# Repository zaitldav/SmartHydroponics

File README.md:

# SmartHydroponics
A controller for small autonomous hydroponics.

## Mindmap

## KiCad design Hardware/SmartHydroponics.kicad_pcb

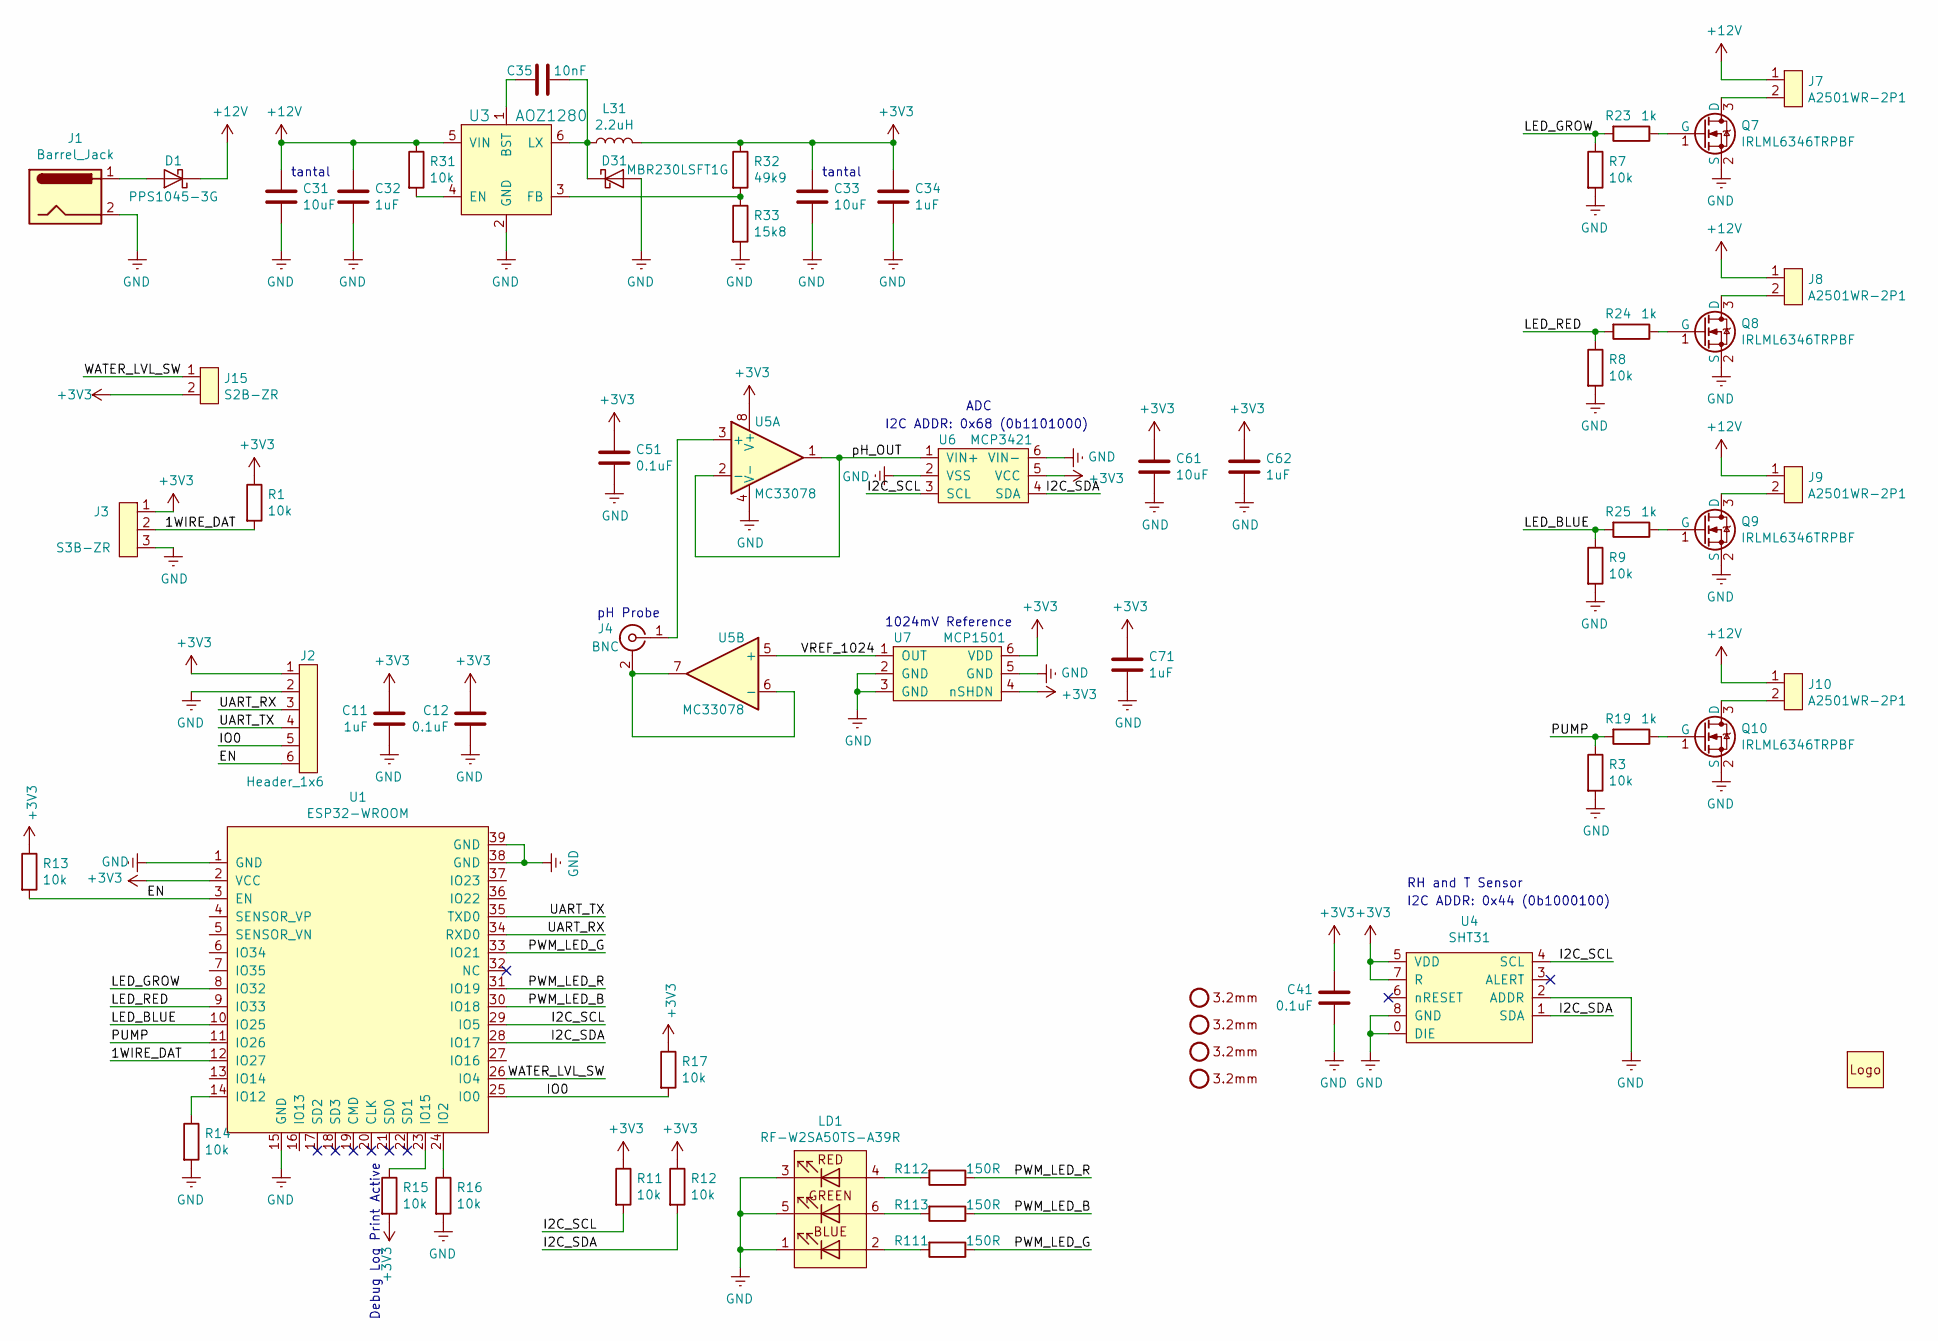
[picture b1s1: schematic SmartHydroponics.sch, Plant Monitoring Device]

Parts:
C11, C32, C34, C62, C71: 1uF; C0603
C12, C41, C51: 0.1uF; C0603
C31, C33, C61: 10uF; C1210
C35: 10nF; C0603
D1: PPS1045-3G; TO-277-3
D31: MBR230LSFT1G; SOD-123
H1, H2, H3, H4: Mounting_hole_unplated_3,2mm
H111: Mr_Gardener_Logo_Small; mr_hydrogardener_logo_12mm
J1: Barrel_Jack; BarrelJack_Horizontal
J2: Header_1x6; Header_1x06_P2.54mm
J3: S3B-ZR
J4: BNC; TE_BNC
J7, J8, J9, J10: A2501WR-2P1
J15: S2B-ZR
L31: 2.2uH; L1210
LD1: RF-W2SA50TS-A39R
Q7, Q8, Q9, Q10: IRLML6346TRPBF; SOT-23
R1, R3, R7, R8, R9, R11, R12, R13, R14, R15, R16, R17, R31: 10k; R0603
R19, R23, R24, R25: 1k; R0603
R32: 49k9; R0603
R33: 15k8; R0603
R111, R112, R113: 150R; R0603
U1: ESP32-WROOM
U3: AOZ1280; SOT-23-6
U4: SHT31
U5: MC33078; SOIC-8
U6: MCP3421; SOT-23-6
U7: MCP1501; SOT-23-6

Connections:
+3V3: C11.1, C12.1, C33.1, C34.1, C41.1, C51.1, C61.1, C62.1, C71.1, J2.1, J3.1, J15.2, L31.2, R1.1, R11.1, R12.1, R13.1, R15.2, R17.1, R32.1, U1.2 (VCC), U4.5 (VDD), U4.7 (R), U5.8 (V+), U6.5 (VCC), U7.4 (nSHDN), U7.6 (VDD)
+12V: C31.1, C32.1, D1.1 (K), J7.1, J8.1, J9.1, J10.1, R31.1, U3.5 (VIN)
/1WIRE_DAT: J3.2, R1.2, U1.12 (IO27)
/EN: J2.6, R13.2, U1.3 (EN)
/I2C_SCL: R11.2, U1.29 (IO5), U4.4 (SCL), U6.3 (SCL)
/I2C_SDA: R12.2, U1.28 (IO17), U4.1 (SDA), U6.4 (SDA)
/IO0: J2.5, R17.2, U1.25 (IO0)
/LED_BLUE: R9.1, R25.2, U1.10 (IO25)
/LED_GROW: R7.1, R23.2, U1.8 (IO32)
/LED_RED: R8.1, R24.2, U1.9 (IO33)
/PUMP: R3.1, R19.2, U1.11 (IO26)
/PWM_LED_B: R113.1, U1.30 (IO18)
/PWM_LED_G: R111.1, U1.33 (IO21)
/PWM_LED_R: R112.1, U1.31 (IO19)
/UART_RX: J2.3, U1.34 (RXD0)
/UART_TX: J2.4, U1.35 (TXD0)
/VREF_1024: U5.5 (+), U7.1 (OUT)
/WATER_LVL_SW: J15.1, U1.26 (IO4)
/pH_OUT: U5.1, U5.2 (-), U6.1 (VIN+)
GND: C11.2, C12.2, C31.2, C32.2, C33.2, C34.2, C41.2, C51.2, C61.2, C62.2, C71.2, D31.2 (A), J1.2, J2.2, J3.3, LD1.1 (K), LD1.3 (K), LD1.5 (K), Q7.2 (S), Q8.2 (S), Q9.2 (S), Q10.2 (S), R3.2, R7.2, R8.2, R9.2, R14.2, R16.2, R33.2, U1.1 (GND), U1.15 (GND), U1.38 (GND), U1.39 (GND), U3.2 (GND), U4.0 (DIE), U4.2 (ADDR), U4.8 (GND), U5.4 (V-), U6.2 (VSS), U6.6 (VIN-), U7.2 (GND), U7.3 (GND), U7.5 (GND)
unnamed: C35.1, U3.1 (BST)
unnamed: C35.2, D31.1 (K), L31.1, U3.6 (LX)
unnamed: D1.2 (A), J1.1
unnamed: J4.1 (In), U5.3 (+)
unnamed: J4.2 (Ext), U5.6 (-), U5.7
unnamed: J7.2, Q7.3 (D)
unnamed: J8.2, Q8.3 (D)
unnamed: J9.2, Q9.3 (D)
unnamed: J10.2, Q10.3 (D)
unnamed: LD1.2 (A), R111.2
unnamed: LD1.4 (A), R112.2
unnamed: LD1.6 (A), R113.2
unnamed: Q7.1 (G), R23.1
unnamed: Q8.1 (G), R24.1
unnamed: Q9.1 (G), R25.1
unnamed: Q10.1 (G), R19.1
unnamed: R14.1, U1.14 (IO12)
unnamed: R15.1, U1.23 (IO15)
unnamed: R16.1, U1.24 (IO2)
unnamed: R31.2, U3.4 (EN)
unnamed: R32.2, R33.1, U3.3 (FB)

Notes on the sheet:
tantal
Debug Log Print Active
I2C ADDR: 0x68 (0b1101000)
ADC
1024mV Reference
pH Probe
I2C ADDR: 0x44 (0b1000100)
RH and T Sensor

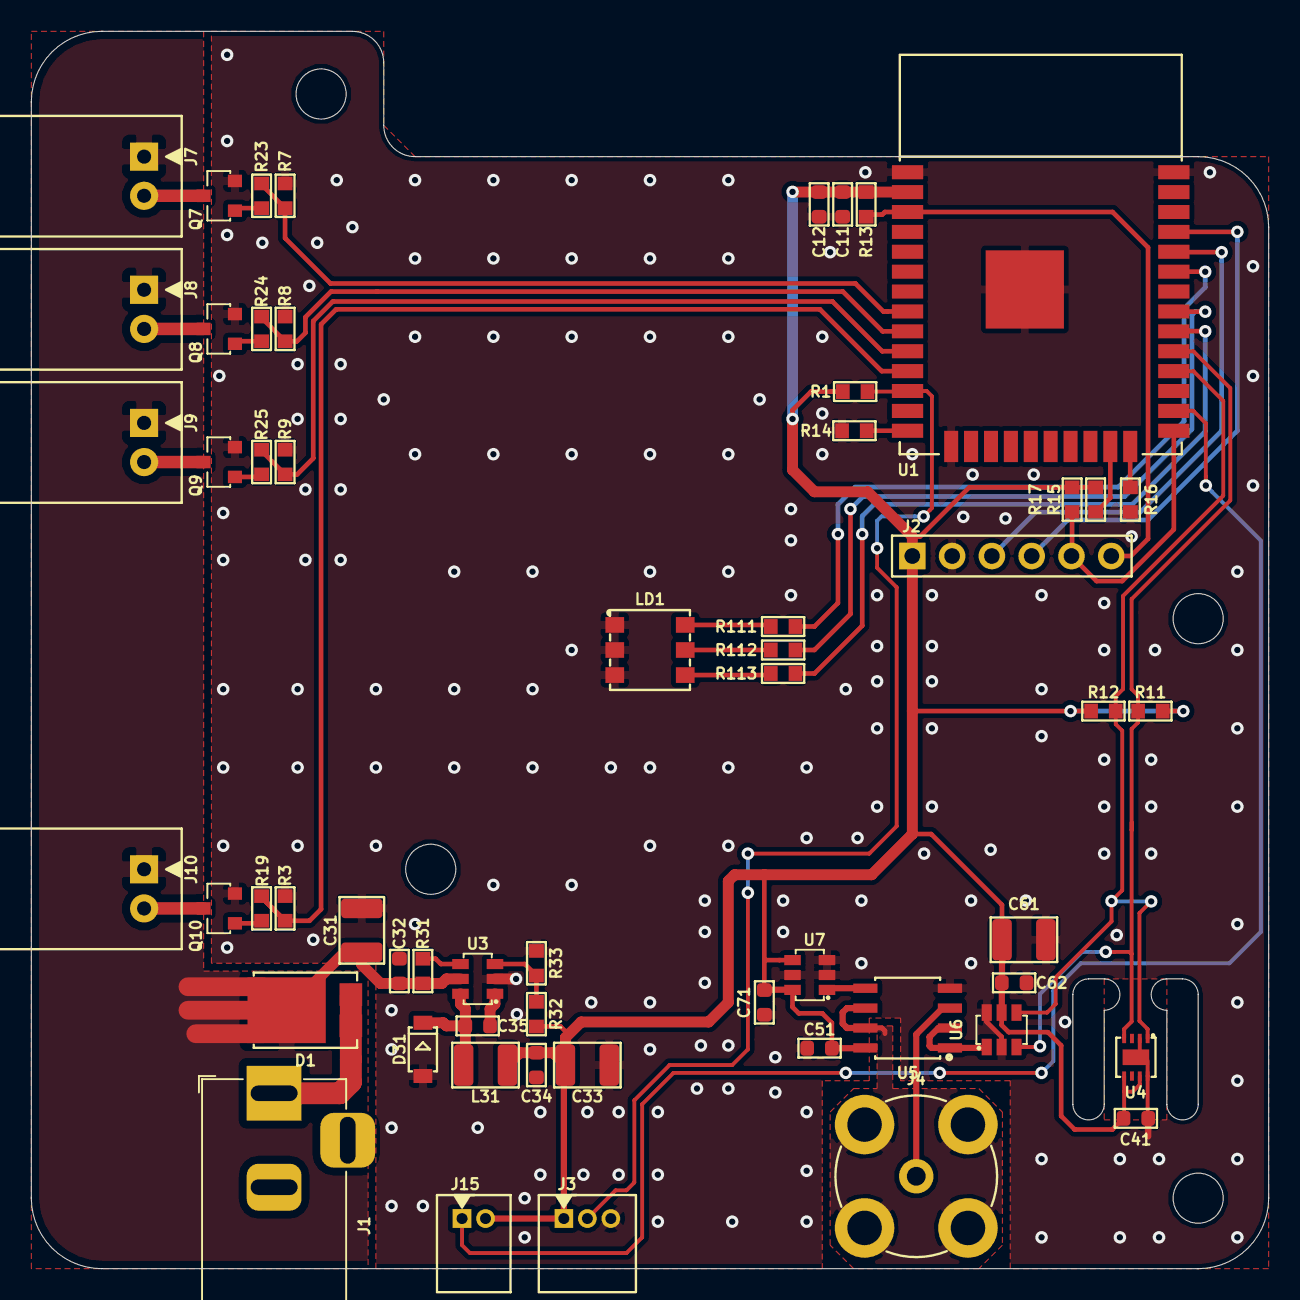
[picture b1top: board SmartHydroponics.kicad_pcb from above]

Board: 2 copper layers, 79.0 x 79.0 mm, 62 parts (1 on the bottom side), 41 nets.

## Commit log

2019-06-18 Modify at https://sketchboard.me/VBDVKRELhSpv
2019-06-28 Created folder for hardware. Started to design the schematics.
2019-06-28 Changes in schematics I didn't push before by accident.
2019-07-19 Created logos for the hydroponics.
2019-07-19 Finished design of the hydroponics controler. Generated Gerbers.
2020-12-07 I do not remember. Sorry. Forgot to push. Sincerely Past David.
